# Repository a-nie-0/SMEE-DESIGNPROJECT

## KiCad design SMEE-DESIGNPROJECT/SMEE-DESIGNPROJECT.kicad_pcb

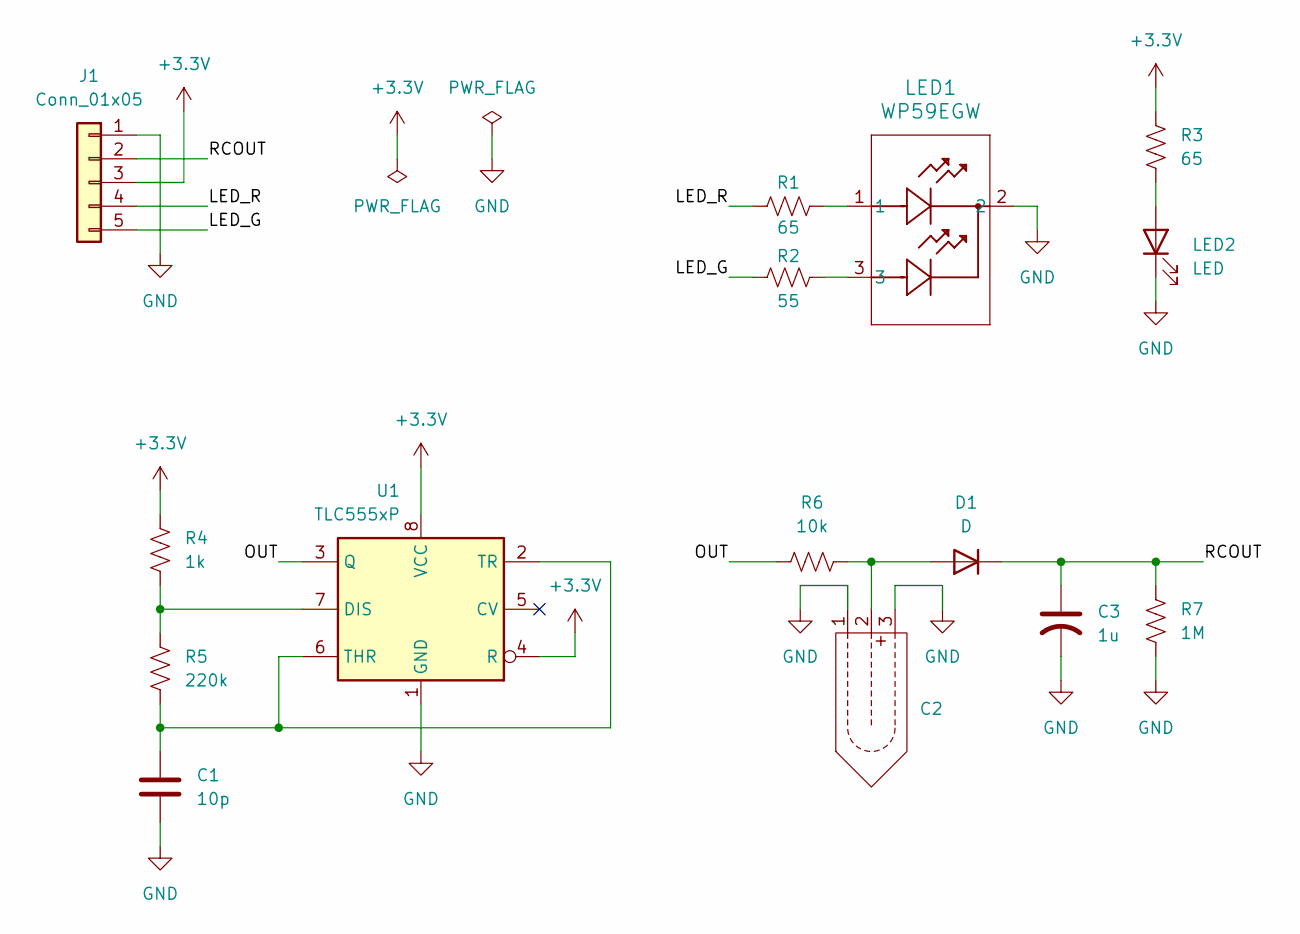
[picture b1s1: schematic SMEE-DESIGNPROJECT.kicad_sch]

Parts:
C1: 10p; C_Disc_D6.0mm_W4.4mm_P5.00mm
C2: SMEE_SOIL_PROBE
C3: 1u; CP_Radial_D5.0mm_P2.00mm
D1: D; D_DO-35_SOD27_P10.16mm_Horizontal
J1: Conn_01x05; PinHeader_1x05_P2.54mm_Horizontal
LED1: WP59EGW; WP59EGW_KNB
LED2: LED; LED_D5.0mm_Clear
R1, R3: 65; R_Axial_DIN0207_L6.3mm_D2.5mm_P10.16mm_Horizontal
R2: 55; R_Axial_DIN0207_L6.3mm_D2.5mm_P10.16mm_Horizontal
R4: 1k; R_Axial_DIN0207_L6.3mm_D2.5mm_P10.16mm_Horizontal
R5: 220k; R_Axial_DIN0207_L6.3mm_D2.5mm_P10.16mm_Horizontal
R6: 10k; R_Axial_DIN0207_L6.3mm_D2.5mm_P10.16mm_Horizontal
R7: 1M; R_Axial_DIN0207_L6.3mm_D2.5mm_P10.16mm_Horizontal
U1: TLC555xP; DIP-8_W7.62mm

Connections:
+3.3V: J1.3, R3.1, R4.1, U1.4 (R), U1.8 (VCC)
/LED_G: J1.5, R2.1
/LED_R: J1.4, R1.1
/OUT: R6.1, U1.3 (Q)
/RCOUT: C3.1, D1.1 (K), J1.2, R7.2
GND: C1.2, C2.1, C2.3, C3.2, J1.1, LED1.2, LED2.1 (K), R7.1, U1.1 (GND)
unnamed: C2.2, D1.2 (A), R6.2
unnamed: LED1.1, R1.2
unnamed: LED1.3, R2.2
unnamed: LED2.2 (A), R3.2
unnamed: R4.2, R5.1, U1.7 (DIS)
unnamed: C1.1, R5.2, U1.2 (TR), U1.6 (THR)

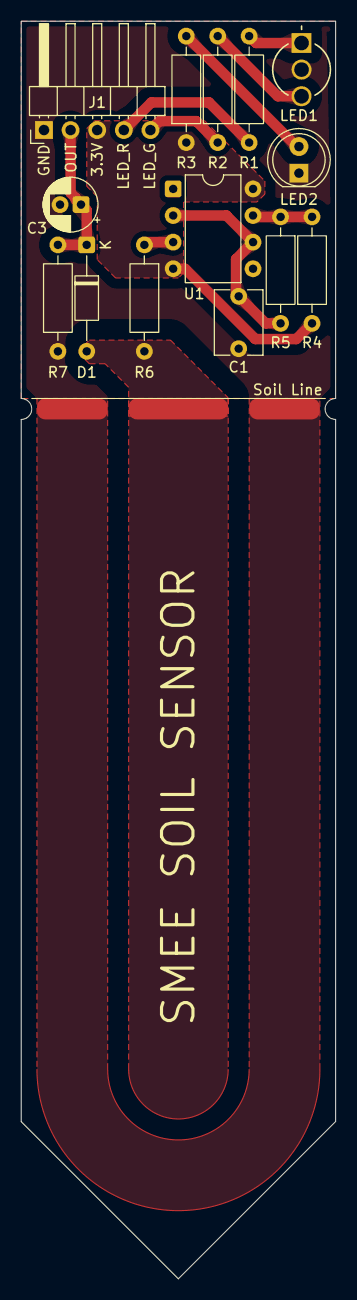
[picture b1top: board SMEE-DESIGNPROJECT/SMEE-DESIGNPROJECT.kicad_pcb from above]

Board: 2 copper layers, 30.0 x 120.0 mm, 15 parts (0 on the bottom side), 12 nets.

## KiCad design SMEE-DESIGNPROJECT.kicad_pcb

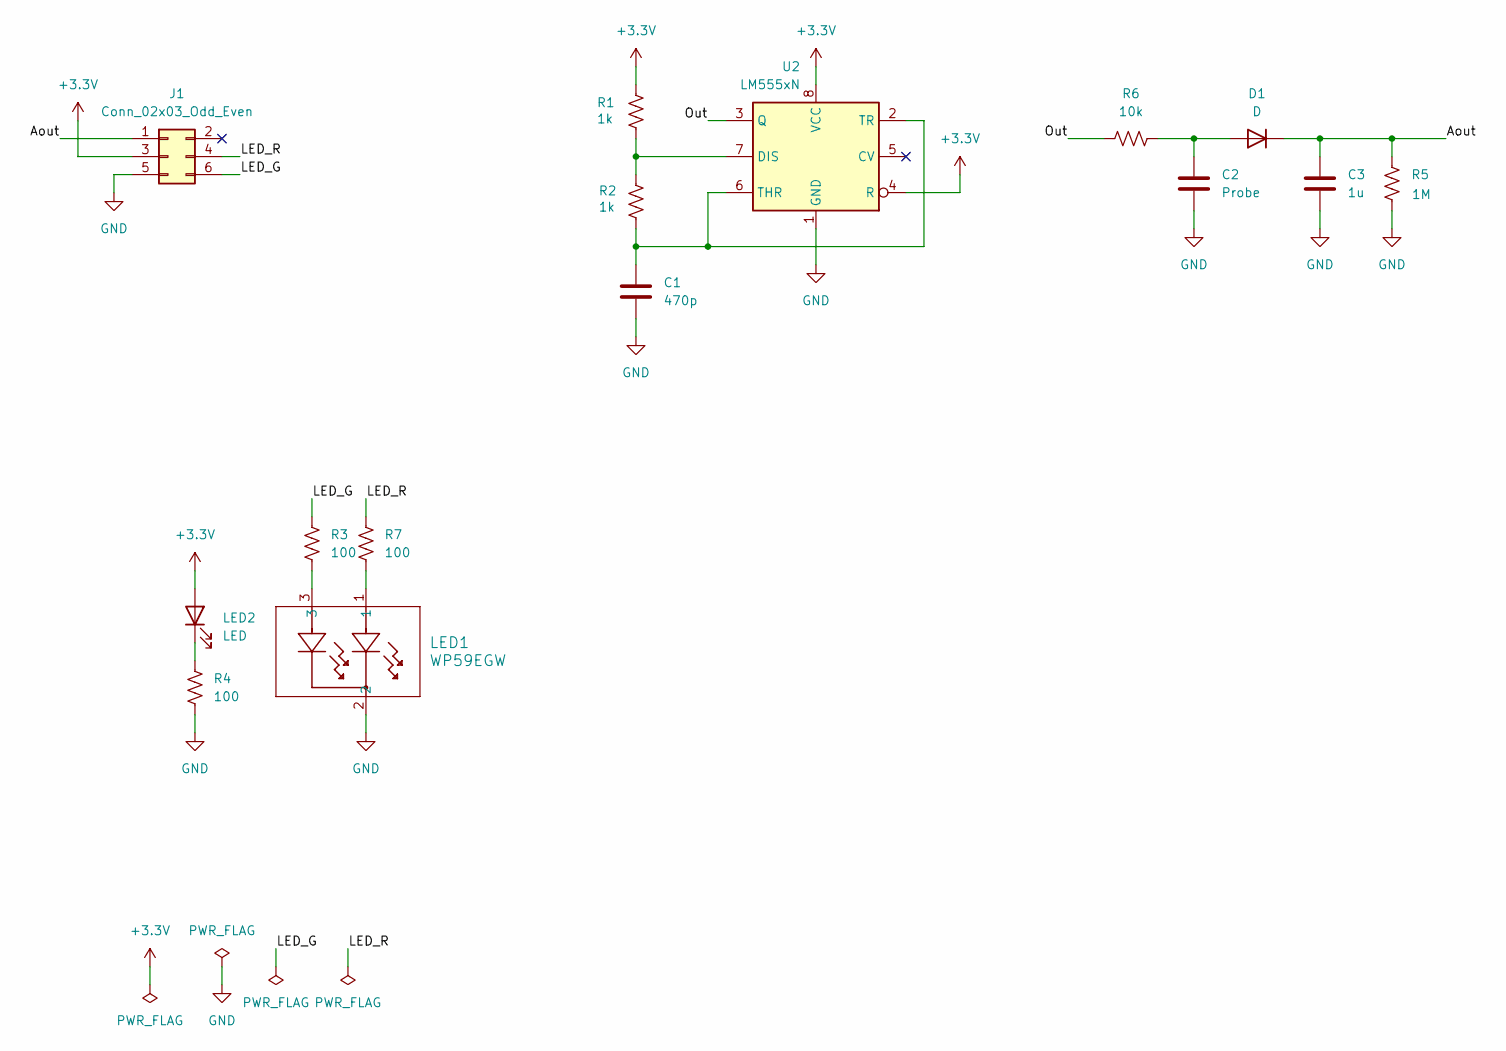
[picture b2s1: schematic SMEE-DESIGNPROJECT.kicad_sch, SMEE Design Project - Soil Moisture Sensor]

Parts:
C1: 470p; C_Disc_D6.0mm_W4.4mm_P5.00mm
C2: Probe; SMEE_Soil_Sensor
C3: 1u; CP_Radial_D5.0mm_P2.50mm
D1: D; D_A-405_P10.16mm_Horizontal
J1: Conn_02x03_Odd_Even; PinHeader_2x03_P2.54mm_Horizontal
LED1: WP59EGW; WP59EGW_KNB
LED2: LED; LED_D5.0mm_Clear
R1, R2: 1k; R_Axial_DIN0207_L6.3mm_D2.5mm_P10.16mm_Horizontal
R3, R4, R7: 100; R_Axial_DIN0207_L6.3mm_D2.5mm_P10.16mm_Horizontal
R5: 1M; R_Axial_DIN0207_L6.3mm_D2.5mm_P10.16mm_Horizontal
R6: 10k; R_Axial_DIN0207_L6.3mm_D2.5mm_P10.16mm_Horizontal
U2: LM555xN; DIP-8_W7.62mm

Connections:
+3.3V: J1.3, LED2.2 (A), R1.1, U2.4 (R), U2.8 (VCC)
/Aout: C3.1, D1.1 (K), J1.1, R5.2
/LED_G: J1.6, R3.2
/LED_R: J1.4, R7.2
/Out: R6.1, U2.3 (Q)
GND: C1.2, C2.2, C3.2, J1.5, LED1.2, R4.2, R5.1, U2.1 (GND)
unnamed: C2.1, D1.2 (A), R6.2
unnamed: LED1.1, R7.1
unnamed: LED1.3, R3.1
unnamed: LED2.1 (K), R4.1
unnamed: R1.2, R2.1, U2.7 (DIS)
unnamed: C1.1, R2.2, U2.2 (TR), U2.6 (THR)

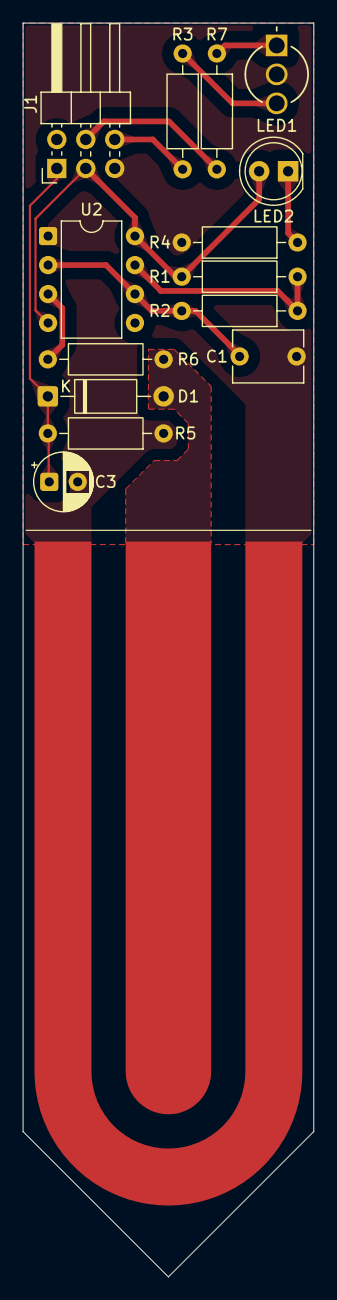
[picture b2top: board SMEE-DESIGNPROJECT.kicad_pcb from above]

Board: 2 copper layers, 25.5 x 110.0 mm, 15 parts (0 on the bottom side), 12 nets.

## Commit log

2026-02-25 Reposition PCB components; add title block & PDFs
2026-02-25 Updated unrouted traces
2026-03-01 Enable teardrops and update PCB geometry
    Add automatic backups and lock file; update KiCad project and PCB to enable teardrops on many pads/vias and adjust copper geometry. This change inserts teardrop settings for numerous pads, adds a tea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
2026-03-01 Update PCB layout and backups
    Change component value (Value: 330 → 100) and perform extensive PCB layout edits: reroute segments, update zone polygons, net assignments, priorities, teardrop attributes, min_thickness/fill settings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
2026-03-02 Update KiCad project: settings and cache cleanup
    Remove temporary autosave and lock files, enable all visible layers in SMEE-DESIGNPROJECT.kicad_prl, and regenerate/truncate fp-info-cache (updated header/hash and removed large footprint entries). T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
2026-03-03 Add PCB fab outputs, backups, and KiCad rules
    Exported fabrication outputs (Gerber, drill, paste, silkscreen, job files and Fab Outputs.zip) from KiCad PCBNew 9.0.4, added PCBWay custom DRC files and fp-info-cache, and committed several project 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
2026-03-10 Add backups; adjust PCB & update footprint cache
    Add several SMEE-DESIGNPROJECT backup .zip files and a temporary schematic lock file. Adjust PCB: move component value (WP59EGW) position. Update project preferences (visible_layers) in .kicad_prl. R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
2026-03-10 Reorganize KiCad project structure
    Remove generated/auxiliary files (datasheets, Fab Outputs/gerbers, many backups and .lck temporary files) and clean up old project artifacts. Add a dedicated SMEE-DESIGNPROJECT-LIBRARIES folder with 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
2026-03-10 Fix KiCad library URIs
    Update sym-lib-table and fp-lib-table to correct local URIs for SMEE_SOIL_PROBE and WP59EGW libraries. The path was changed to include the SMEE-DESIGNPROJECT parent folder under Downloads, repairing 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
2026-03-11 Adjust footprints, stackup, and project metadata
    Small KiCad project updates: tweak SMEE_SOIL_PROBE silkscreen lines and text positions (added B.SilkS line), update WP59EGW_KNB 3D model path and Z offset, and add a detailed board stackup to the .ki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
2026-03-11 Adjust PCB footprints, traces and copper zones
    Modify SMEE-DESIGNPROJECT.kicad_pcb to tweak component placements (small XY adjustments for axial resistor and diode), adjust trace segments (endpoints, added short segments, updated UUIDs), and reor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
2026-03-11 Add fabrication outputs; tweak footprint
    Adjust SMD pad geometry in SMEE_SOIL_PROBE.kicad_mod (minor position/size changes). Add generated fabrication outputs (Gerbers, drill files, edge cuts) and a ZIP export. Update project files (.kicad_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
2026-03-12 Enable teardrops on pads and add teardrop zones
    Enable teardrops for numerous pads in SMEE-DESIGNPROJECT.kicad_pcb (added teardrops blocks with parameters like best_length_ratio, max_length, best_width_ratio, max_width, filter_ratio, enabled, allo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
2026-03-12 SMEE PCB: renumber nets, adjust zones & footprints
    Remove/replace old backup zips and add lock files; update SMEE-DESIGNPROJECT.kicad_pcb with net renumbering and reassignments, footprint position/UUID tweaks, trace segment coordinate changes, and zo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
2026-03-12 Update KiCad footprints, active layer, and backups
    Remove two old backup ZIPs and add two new timestamped backups in SMEE-DESIGNPROJECT/SMEE-DESIGNPROJECT-backups. Change board active_layer from 5 to 0 in SMEE-DESIGNPROJECT.kicad_prl. Update two foot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
2026-03-12 Update PCB footprints, positions and UUIDs
    Add a project backup ZIP and apply multiple KiCad PCB updates: replace many element UUIDs, adjust component positions/rotations (notably LED2 and a radial capacitor footprint changed to 2.00mm pitch)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
2026-03-15 Add PCB backup, remove ratsnest, delete lock file
    Add a new KiCad project backup (SMEE-DESIGNPROJECT-2026-03-16_011510.zip), remove the "ratsnest" entry from SMEE-DESIGNPROJECT.kicad_prl to exclude ratsnest from the render/order list, and delete the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
2026-03-16 Adjust PCB comment positions and labels
    Update minor silkscreen/comment changes in SMEE-DESIGNPROJECT.kicad_pcb: shift two comment line endpoints from y=85 to y=86 and update their gr_text labels/positions ("85"→"84" at y 127.5→128, "35"→"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
2026-03-16 Update PCB zones, nets, and teardrops
    Refactor multiple F.Cu zone definitions in SMEE-DESIGNPROJECT.kicad_pcb: reassign net numbers/names, update zone UUIDs and priorities, and standardize teardrop (padvia) attributes. Several zone polyg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
2026-03-18 Update PCB routing and zones; add backups
    Adjust PCB layout: reroute several segments and update net assignments around U1 and LED footprints, modify zone definitions (net names, priorities, UUIDs, polygons and filled_polygons) and add teard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
2026-03-18 Add project backup archive (2026-03-18)
    Add binary backup ZIP of SMEE-DESIGNPROJECT created on 2026-03-18_13:51:50 to the SMEE-DESIGNPROJECT-backups folder. This is a restore point and does not modify source files.
2026-03-19 Update schematic values and add backup
    Modify several component values in SMEE-DESIGNPROJECT.kicad_sch to new expected values (1k -> 470, 220k -> 2.2k, 65 -> 150, 55 -> 140, 10p -> 470p). Add a timestamped project backup ZIP (SMEE-DESIGNP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
2026-03-19 Add backup zip and remove KiCad lock file
    Add a timestamped project backup (SMEE-DESIGNPROJECT-2026-03-19_130100.zip) to the backups folder and remove the transient KiCad schematic lock file (~SMEE-DESIGNPROJECT.kicad_sch.lck) to avoid commi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
